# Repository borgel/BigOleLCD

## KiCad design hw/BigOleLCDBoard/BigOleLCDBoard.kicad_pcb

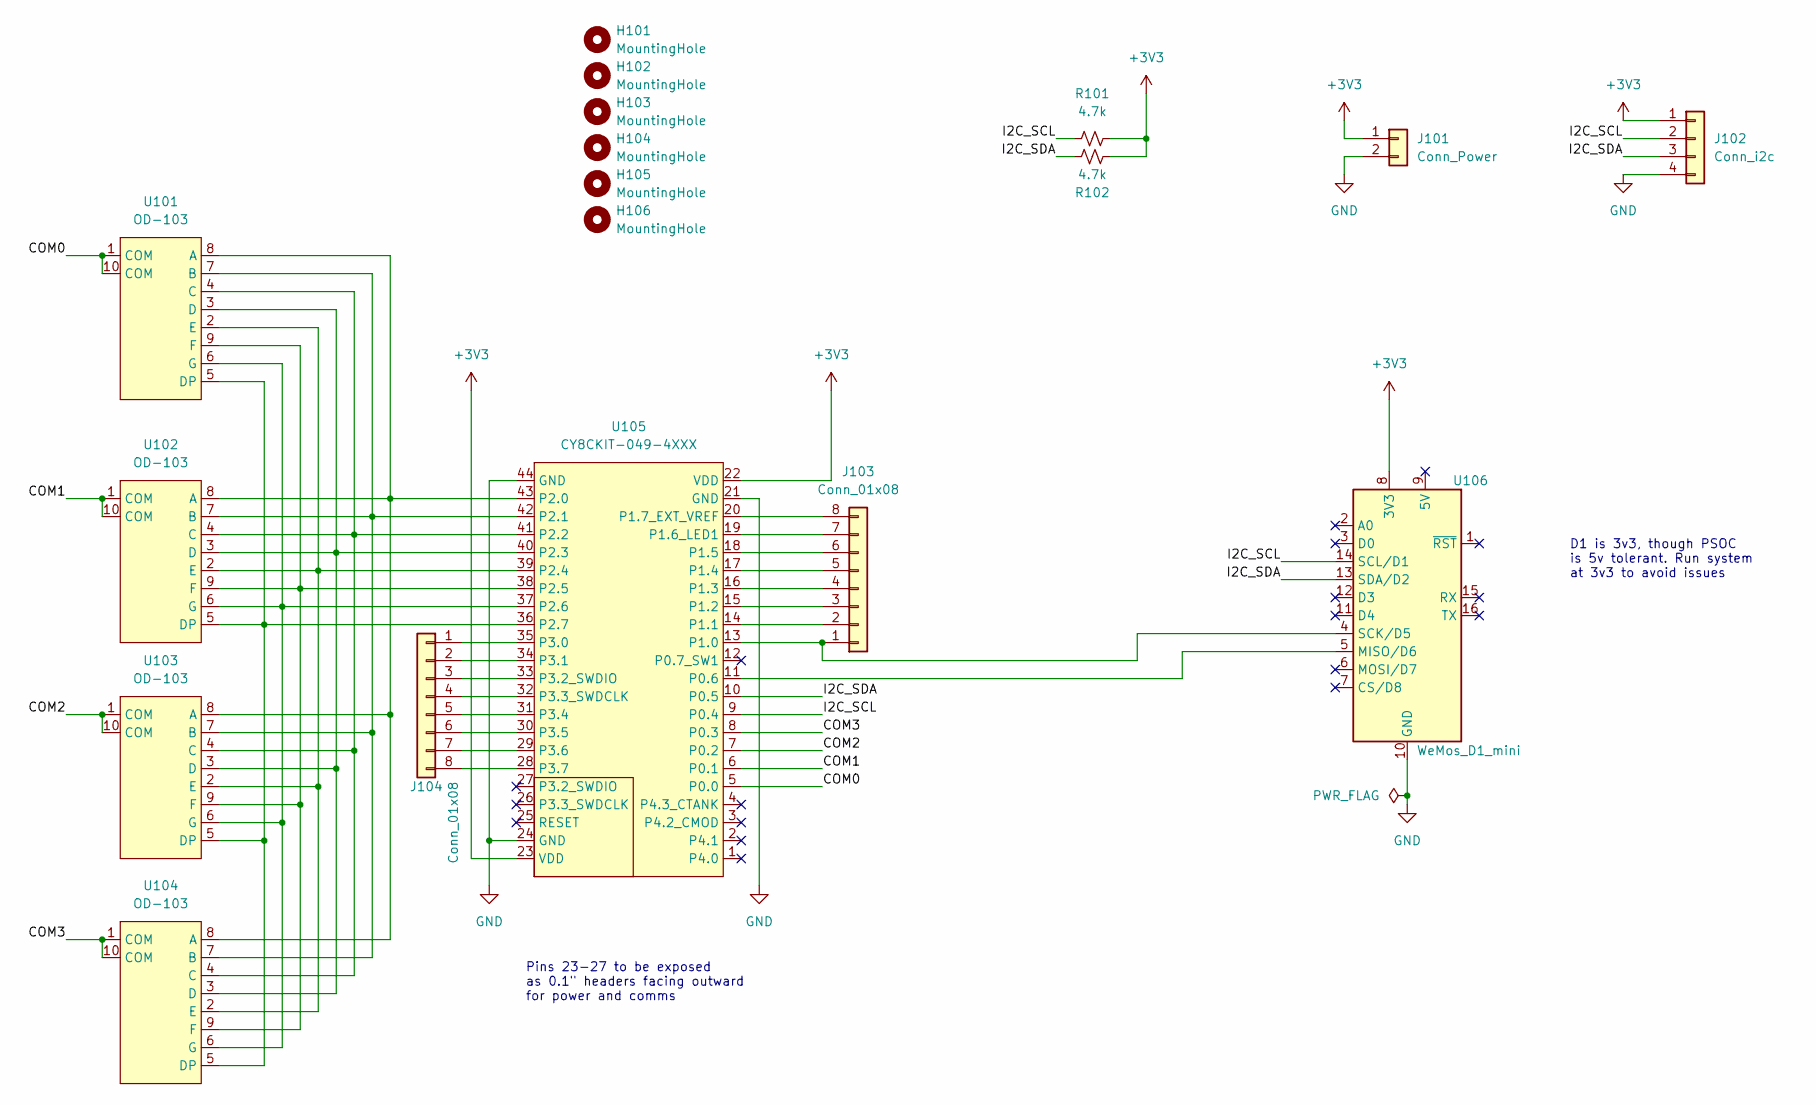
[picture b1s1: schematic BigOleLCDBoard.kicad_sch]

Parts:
H101, H102, H103, H104, H105, H106: MountingHole; MountingHole_4.3mm_M4
J101: Conn_Power; PinHeader_1x02_P2.54mm_Vertical
J102: Conn_i2c; PinHeader_1x04_P2.54mm_Vertical
J103, J104: Conn_01x08; PinHeader_1x08_P2.54mm_Vertical
R101, R102: 4.7k; R_0805_2012Metric_Pad1.20x1.40mm_HandSolder
U101, U102, U103, U104: OD-103
U105: CY8CKIT-049-4XXX; CY8CKIT-049-42XX
U106: WeMos_D1_mini; WEMOS_D1_mini_light

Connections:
+3V3: J101.1, J102.1, R101.2, R102.1, U105.22 (VDD), U105.23 (VDD), U106.8 (3V3)
/COM0: U101.1 (COM), U101.10 (COM), U105.5 (P0.0)
/COM1: U102.1 (COM), U102.10 (COM), U105.6 (P0.1)
/COM2: U103.1 (COM), U103.10 (COM), U105.7 (P0.2)
/COM3: U104.1 (COM), U104.10 (COM), U105.8 (P0.3)
/I2C_SCL: J102.2, R101.1, U105.9 (P0.4), U106.14 (SCL/D1)
/I2C_SDA: J102.3, R102.2, U105.10 (P0.5), U106.13 (SDA/D2)
GND: J101.2, J102.4, U105.21 (GND), U105.24 (GND), U105.44 (GND), U106.10 (GND)
unnamed: J103.1, U105.13 (P1.0), U106.4 (SCK/D5)
unnamed: J103.2, U105.14 (P1.1)
unnamed: J103.3, U105.15 (P1.2)
unnamed: J103.4, U105.16 (P1.3)
unnamed: J103.5, U105.17 (P1.4)
unnamed: J103.6, U105.18 (P1.5)
unnamed: J103.7, U105.19 (P1.6_LED1)
unnamed: J103.8, U105.20 (P1.7_EXT_VREF)
unnamed: J104.1, U105.35 (P3.0)
unnamed: J104.2, U105.34 (P3.1)
unnamed: J104.3, U105.33 (P3.2_SWDIO)
unnamed: J104.4, U105.32 (P3.3_SWDCLK)
unnamed: J104.5, U105.31 (P3.4)
unnamed: J104.6, U105.30 (P3.5)
unnamed: J104.7, U105.29 (P3.6)
unnamed: J104.8, U105.28 (P3.7)
unnamed: U101.2 (E), U102.2 (E), U103.2 (E), U104.2 (E), U105.39 (P2.4)
unnamed: U101.3 (D), U102.3 (D), U103.3 (D), U104.3 (D), U105.40 (P2.3)
unnamed: U101.4 (C), U102.4 (C), U103.4 (C), U104.4 (C), U105.41 (P2.2)
unnamed: U101.5 (DP), U102.5 (DP), U103.5 (DP), U104.5 (DP), U105.36 (P2.7)
unnamed: U101.6 (G), U102.6 (G), U103.6 (G), U104.6 (G), U105.37 (P2.6)
unnamed: U101.7 (B), U102.7 (B), U103.7 (B), U104.7 (B), U105.42 (P2.1)
unnamed: U101.8 (A), U102.8 (A), U103.8 (A), U104.8 (A), U105.43 (P2.0)
unnamed: U101.9 (F), U102.9 (F), U103.9 (F), U104.9 (F), U105.38 (P2.5)
unnamed: U105.11 (P0.6), U106.5 (MISO/D6)

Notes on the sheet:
Pins 23-27 to be exposed as 0.1" headers facing outward for power and comms
D1 is 3v3, though PSOC is 5v tolerant. Run system at 3v3 to avoid issues

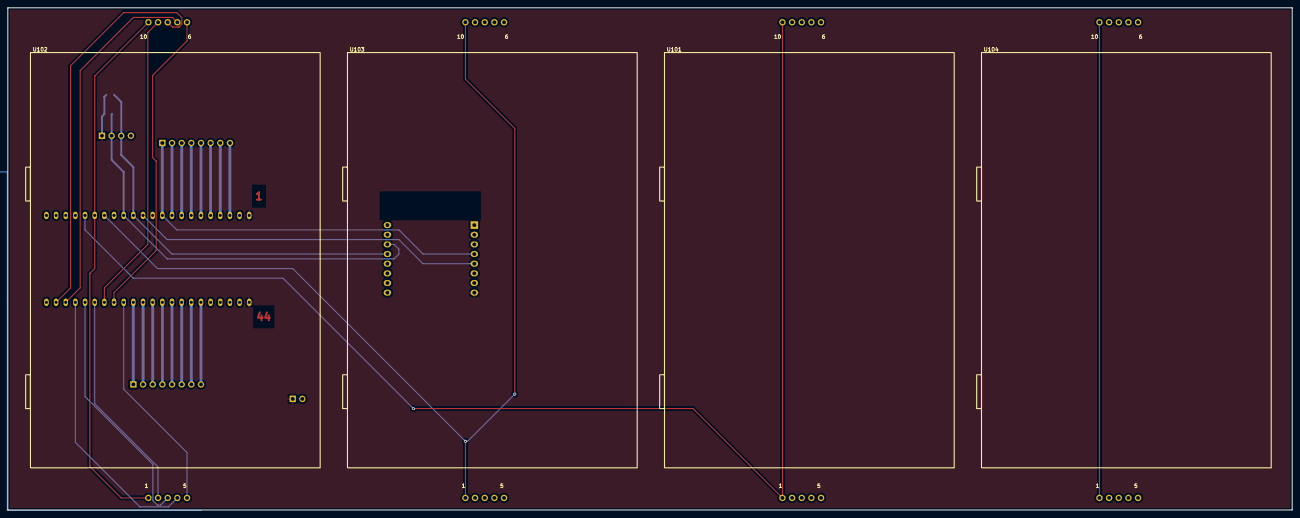
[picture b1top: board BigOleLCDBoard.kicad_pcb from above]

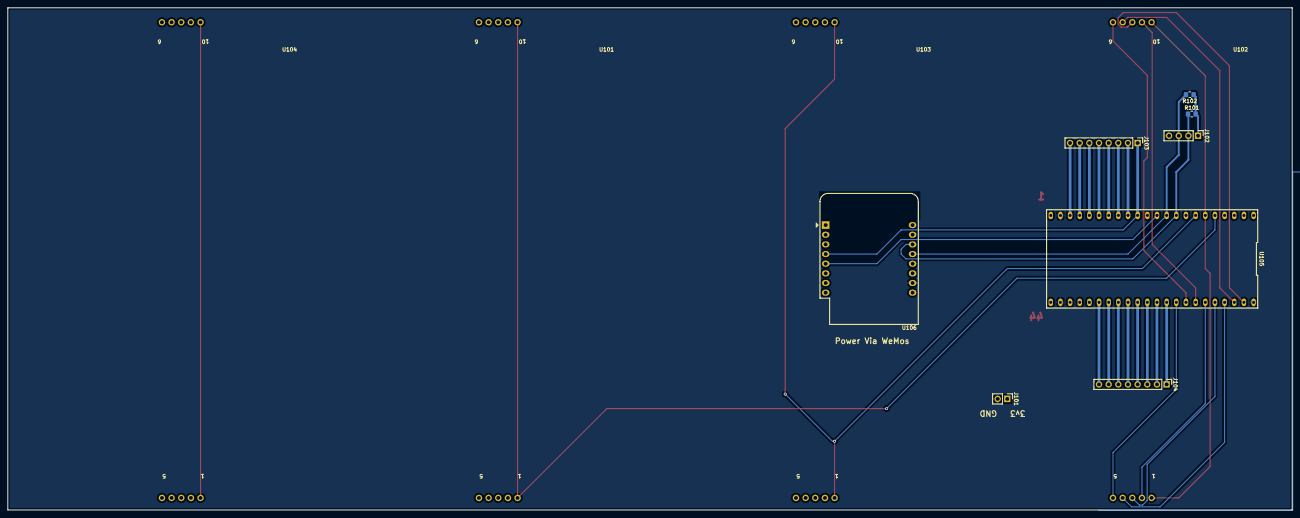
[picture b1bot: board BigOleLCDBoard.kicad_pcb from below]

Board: 2 copper layers, 337.8 x 132.1 mm, 18 parts (8 on the bottom side), 33 nets.

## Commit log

2022-02-22 Initial commit
    PSOC proof of concept
2022-02-22 Starting KiCAD
2022-02-22 Add datasheets
2022-02-22 Update PSOC with full pinmapping
2022-02-22 Schematic complete
2022-02-22 Starting layout
2022-02-25 Ask WeMos D1-Mini, start layout
2022-02-25 Ignore KiCAD Backups
